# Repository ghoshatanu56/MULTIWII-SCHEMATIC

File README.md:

# MULTIWII-SCHEMATIC-UPDATED
INCLUDES MPU-6050,BMP 180,HMC 5883L
CHANGES FROM PREVIOUS INCLUDES ADDITION OF I2C PULL UP RESISTORS,TX ,RX LED ONBOARD

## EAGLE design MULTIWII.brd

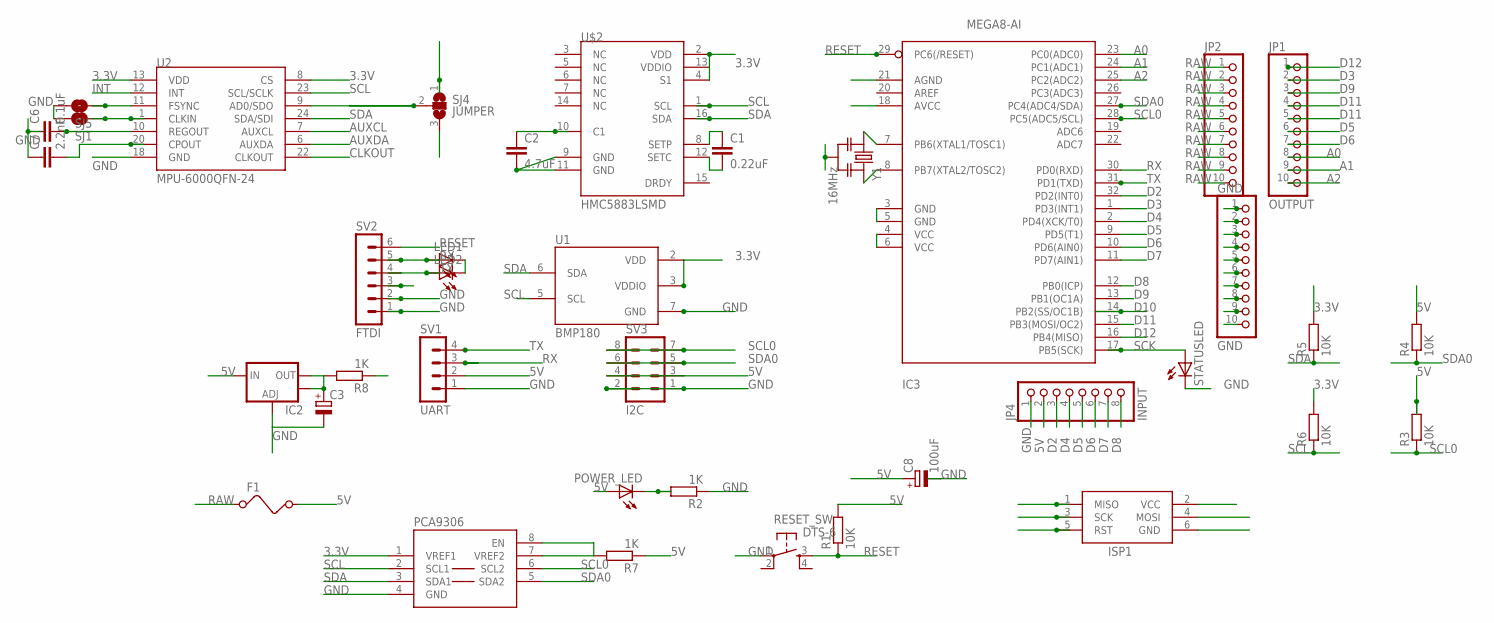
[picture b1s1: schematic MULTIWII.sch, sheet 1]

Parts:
C1: 0.22uF; C0805
C2: 4.7uF; C0805
C3: CPOL-EUA/3216-18R; A/3216-18R
C6: 0.1uF; C0805
C7: 2.2nF; C0805
C8: 100uF; CT7343
F1: FUSEF; 1812
GND: GND; 1X10
IC2: V_REG_LM1117SOT223; SOT223
IC3: MEGA8-AI; TQFP32-08
ISP1: AVRISP-6; AVRISP
JP1: OUTPUT; 1X10
JP2: PINHD-1X10; 1X10
JP4: INPUT; 1X08
LED1, LED2: LEDCHIPLED_0805; CHIPLED_0805
PCA9306: PCA9306; PSOP-8
POWER_LED: LEDCHIPLED_1206; CHIPLED_1206
R1, R3, R4, R5, R6: 10K; M0805
R2, R7, R8: 1K; M0805
RESET_SW: DTS-6
SJ1, SJ5: SOLDERJUMPERNC; SJ_2S
SJ4: JUMPER; SJ_2
STATUSLED: LEDCHIP-LED0805; CHIP-LED0805
SV1: UART; MA04-1
SV2: FTDI; MA06-1
SV3: I2C; MA04-2
U1: BMP180
U2: MPU-6000QFN-24; QFN-24-TESTING
U$2: HMC5883LSMD; 16LPCC
Y1: 16MHz; RESONATOR_MURATA3

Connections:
3.3V: PCA9306.1 (VREF1), R5.2, R6.2, R8.1, SJ4.1, U1.2 (VDD), U1.3 (VDDIO), U2.8 (CS), U2.13 (VDD), U$2.2 (VDD), U$2.4 (S1), U$2.13 (VDDIO)
5V: C8.+, F1.2, IC2.3 (IN), IC3.4 (VCC), IC3.6 (VCC), IC3.18 (AVCC), ISP1.2 (VCC), JP4.2, POWER_LED.A, R1.2, R3.2, R4.2, R7.1, SV1.2, SV3.3, SV3.4
A0: IC3.23 (PC0(ADC0)), JP1.8
A1: IC3.24 (PC1(ADC1)), JP1.9
A2: IC3.25 (PC2(ADC2)), JP1.10
AD0: SJ4.2, U2.9 (AD0/SDO)
AUXCL: U2.7 (AUXCL)
AUXDA: U2.6 (AUXDA)
C1: C2.1, U$2.10 (C1)
CLKOUT: U2.22 (CLKOUT)
D2: IC3.32 (PD2(INT0)), JP4.3
D3: IC3.1 (PD3(INT1)), JP1.2
D4: IC3.2 (PD4(XCK/T0)), JP4.4
D5: IC3.9 (PD5(T1)), JP1.6, JP4.5
D6: IC3.10 (PD6(AIN0)), JP1.7, JP4.6
D7: IC3.11 (PD7(AIN1)), JP4.7
D8: IC3.12 (PB0(ICP)), JP4.8
D9: IC3.13 (PB1(OC1A)), JP1.3
D10: IC3.14 (PB2(SS/OC1B)), JP1.4
D11: IC3.15 (PB3(MOSI/OC2)), ISP1.4 (MOSI), JP1.5
D12: IC3.16 (PB4(MISO)), ISP1.1 (MISO), JP1.1
GND: C2.2, C3.-, C6.1, C7.1, C8.-, GND.1, GND.2, GND.3, GND.4, GND.5, GND.6, GND.7, GND.8, GND.9, GND.10, IC2.1 (ADJ), IC3.3 (GND), IC3.5 (GND), IC3.21 (AGND), ISP1.6 (GND), JP4.1, LED1.C, LED2.C, PCA9306.4 (GND), R2.1, RESET_SW.1, SJ1.2, SJ4.3, SJ5.2, STATUSLED.C, SV1.1, SV2.1, SV2.2, SV3.1, SV3.2, U1.7 (GND), U2.18 (GND), U$2.9 (GND), U$2.11 (GND), Y1.2
INT: U2.12 (INT)
unnamed: C7.2, U2.20 (CPOUT)
unnamed: C3.+, IC2.2 (OUT), IC2.4 (OUT), R8.2
unnamed: IC3.7 (PB6(XTAL1/TOSC1)), Y1.1
unnamed: C1.1, U$2.8 (SETP)
unnamed: C1.2, U$2.12 (SETC)
unnamed: PCA9306.7 (VREF2), PCA9306.8 (EN), R7.2
unnamed: IC3.8 (PB7(XTAL2/TOSC2)), Y1.3
unnamed: POWER_LED.C, R2.2
unnamed: SJ5.1, U2.11 (FSYNC)
unnamed: SJ1.1, U2.1 (CLKIN)
unnamed: C6.2, U2.10 (REGOUT)
RAW: F1.1, JP2.1, JP2.2, JP2.3, JP2.4, JP2.5, JP2.6, JP2.7, JP2.8, JP2.9, JP2.10, SV2.3
RESET: IC3.29 (PC6(/RESET)), ISP1.5 (RST), R1.1, RESET_SW.3, SV2.6
RX: IC3.30 (PD0(RXD)), LED1.A, SV1.3, SV2.5
SCK: IC3.17 (PB5(SCK)), ISP1.3 (SCK), STATUSLED.A
SCL: PCA9306.2 (SCL1), R6.1, U1.5 (SCL), U2.23 (SCL/SCLK), U$2.1 (SCL)
SCL0: IC3.28 (PC5(ADC5/SCL)), PCA9306.6 (SCL2), R3.1, SV3.7, SV3.8
SDA: PCA9306.3 (SDA1), R5.1, U1.6 (SDA), U2.24 (SDA/SDI), U$2.16 (SDA)
SDA0: IC3.27 (PC4(ADC4/SDA)), PCA9306.5 (SDA2), R4.1, SV3.5, SV3.6
TX: IC3.31 (PD1(TXD)), LED2.A, SV1.4, SV2.4

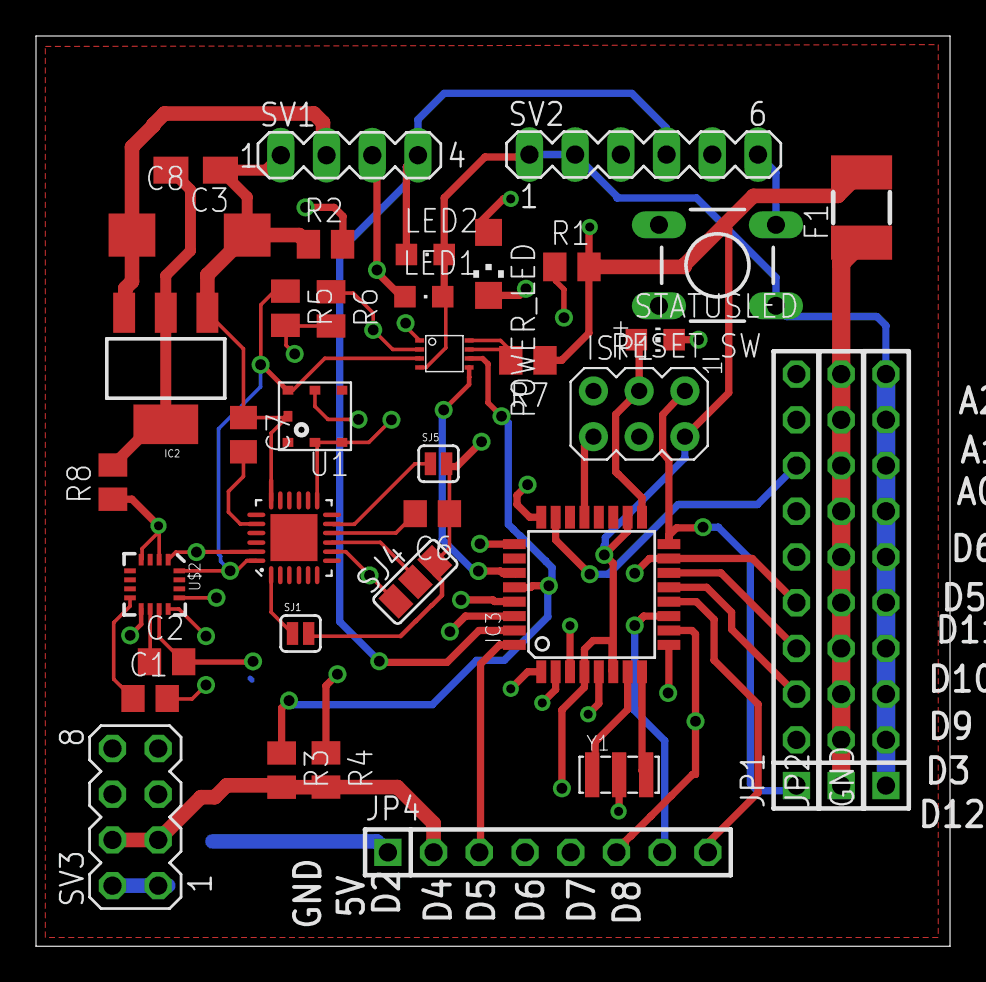
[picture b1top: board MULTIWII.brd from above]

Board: 4 copper layers, 50.8 x 50.6 mm, 38 parts (0 on the bottom side), 39 nets.

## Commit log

2015-08-14 modified: MULTIWII.brd modified: MULTIWII.sch

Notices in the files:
parts and their libraries:
SparkFun-Sensors: Licensing: CC v3.0 Share-Alike You are welcome to use this library for commercial purposes.
m-pad-2.1: License : GNU General Public License version 2 (see bottom)
